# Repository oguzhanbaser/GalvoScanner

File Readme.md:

# Tubitak 1002 Projesi kapsamında geliştirilen Galbo Taraycılı Haberleşme Sistemi

## Genel Amaç
Galvo tabanlı optik yönlendirme, kamera kalibrasyonu, lazer/LED sürücü kartları ve simülasyon (Gazebo) bileşenlerini içeren çok bileşenli Ar-Ge çalışma alanı.

## Dizın Özeti
```
Softwares/
  calib_images/        (İlk kamera kalibrasyon ham görüntüleri)
  new_calib/           (Yeni kalibrasyon çekimleri)
  images/              (Deney / mesafe / çıktı görüntü setleri)
  esp_software/
    main_drv8825.cpp.bak.cpp   (DRV8825 step/dir sürücüsü için yedek ana kod)
    esp32-stepper/             (PlatformIO ESP32 step motor kontrol projesi)
    python-test/
      test1.py                 (Seri / kontrol test scripti)
      myenv*/                  (Yerel sanal ortam klasörleri - repoda tutulması gerekmez)
  opencv-ws/
    camera_calib.py            (Genel kalibrasyon scripti)
    camera_calib_real.py       (Gerçek donanım verisi ile kalibrasyon)
    camera_params.py           (Örnek/çıktı parametre dosyası)
    camera_params_rpi.py       (Raspberry Pi için parametre varyasyonu)
    find_focal_len.py          (Odak uzunluğu yaklaşık hesabı)
    my_utils.py                (Ortak yardımcı fonksiyonlar)
    test*.py / test*_iter.py   (Deneme / iteratif test scriptleri)
    images/, files/, __pycache__/ (Veri ve derleme çıktıları)
  rpi_calib/
    calib_images/              (Raspberry Pi kamera kalibrasyon görüntüleri)

Gazebo-Sim/
  my_test_pkg/
    CMakeLists.txt             (ROS paketi derleme tanımı)
    package.xml                (ROS paket meta verisi)
    launch/camera_gazebo.launch (Kamera modelini Gazebo’da başlatma)
    urdf/camera_model.xacro    (Parametrik kamera URDF/Xacro modeli)
    src/                       (Şu an boş / ileride eklenecek)

Devreler/
  beacon_led/
    led_tester*/               (LED test kartı revizyonları - KiCad .kicad_pcb/.kicad_sch)
    led_tester_v2/led_cnc/     (CNC üretim G-code çıktıları)
    led_tester_v2/production/  (BOM, konum, gerber paketleri)
  esp_stepper/
    esp_stepper.*              (ESP tabanlı stepper sürücü kart şematik & PCB)
    kicad_esp/                 (Espressif kütüphane paketi - footprint/simge)
    libs/pcb, libs/sch         (Özel footprint/schematic kütüphaneleri)
    outputs/                   (PDF çizimler)
    production/                (Üretim dosyaları, yedekler)
  laser_com/
    board/                     (Ön/alternatif ethernet tabanlı taslak kart)
    laser_com_v1/              (Lazer iletişim kartı modüler şemalar: laser_driver, regulator, step_up, fotodiyot)
    production/, output/, libs/ (Üretim & kütüphane)

```

## Önemli Bileşenler
- Kamera Kalibrasyonu: Softwares/opencv-ws/* (Chessboard / iç parametre türetme)
- ESP32 Step Motor Kontrolü: Softwares/esp_software/esp32-stepper (Galvo veya mekanik tarayıcı prototip sürüşü)
- Donanım Kartları: Devreler/* (LED beacon, stepper sürücü, lazer iletişim)
- Simülasyon: Gazebo-Sim/my_test_pkg (Kamera modelleme & ileride galvo sim eklenebilir)
- Kalibrasyon Görselleri: calib_images, new_calib, rpi_calib/calib_images (Distorsiyon/fütür LUT üretim girdileri)

## Kurulum (ESP32 Firmware - PlatformIO)
```
cd Softwares/esp_software/esp32-stepper
pio run
pio run -t upload
pio device monitor
```

## Kamera Kalibrasyon Akışı (Örnek)
1. Satranç tahtası görüntülerini calib_images/ veya new_calib/ altına koy.  
2. opencv-ws dizinine geç:
```
cd Softwares/opencv-ws
python camera_calib.py
```
3. Üretilen parametreleri (örn. camera_params.py) uygulama tarafında içe aktar.  
4. Raspberry Pi için ayrı parametre gerekirse camera_params_rpi.py referans alınır.

## Gazebo Simülasyonu
```
cd Gazebo-Sim/my_test_pkg
# ROS ortamını kaynakla (ör: source /opt/ros/<distro>/setup.bash)
roslaunch my_test_pkg camera_gazebo.launch
```
camera_model.xacro içindeki parametrelerle sanal kamera testleri yapılır.

## Donanım Üretim Notları
- production/ klasörleri: BOM (bom.csv), yerleşim (positions.csv), gerber paketleri (.zip)
- pcb & sch kütüphane dosyalarını libs/ altına izole ederek sürüm kontrolü yapılmış.
- Büyük revizyonlarda outputs/ PDF çizimleri referans saklama.

## Temizlik / .gitignore Önerisi
Aşağıdakiler repoda tutulmayabilir:
- __pycache__/, *.pyc
- Softwares/esp_software/esp32-stepper/.pio/
- Softwares/esp_software/python-test/myenv*/ (sanal ortamlar)
- Büyük ham görüntüler (Git LFS ile: *.jpg)

Örnek ekleme:
```
__pycache__/
*.pyc
.pio/
myenv*/
*.bak.*
```

## Olası Geliştirmeler
- Otomatik kalibrasyon raporu (Markdown çıktısı)
- Galvo açı ↔ piksel koordinat eşleştirme modülü
- ROS düğümü: gerçek donanım + simülasyon arayüzü
- Lazer iletişim protokol dokümantasyonu (ayrı docs/ önerilir)

## Lisans
(Lisans dosyası eklenmeli: MIT / Apache-2.0 / GPL seçilmemiş.)

## Katkı
Fork -> feature branch -> PR.  
İsimlendirme: feat-*, fix-*, doc-*.

## Uyarı
main_drv8825.cpp.bak.cpp ve büyük görüntü setleri sürüm geçmişini şişirebilir; gerekirse arşivleyin veya LFS.

## Hızlı Başlangıç
```
git clone <repo-url>
cd GalvoScanner
# ESP32
cd Softwares/esp_software/esp32-stepper && pio run
# Kalibrasyon
cd ../../opencv-ws && python camera_calib.py
```

## İletişim
Sorumlu / Ekip: (ekleyin)  
E-posta: (ekleyin)

---
Bu README mevcut görünen dizin yapısına göre derlenmiştir; yeni klasörler eklendikçe güncellenmelidir.

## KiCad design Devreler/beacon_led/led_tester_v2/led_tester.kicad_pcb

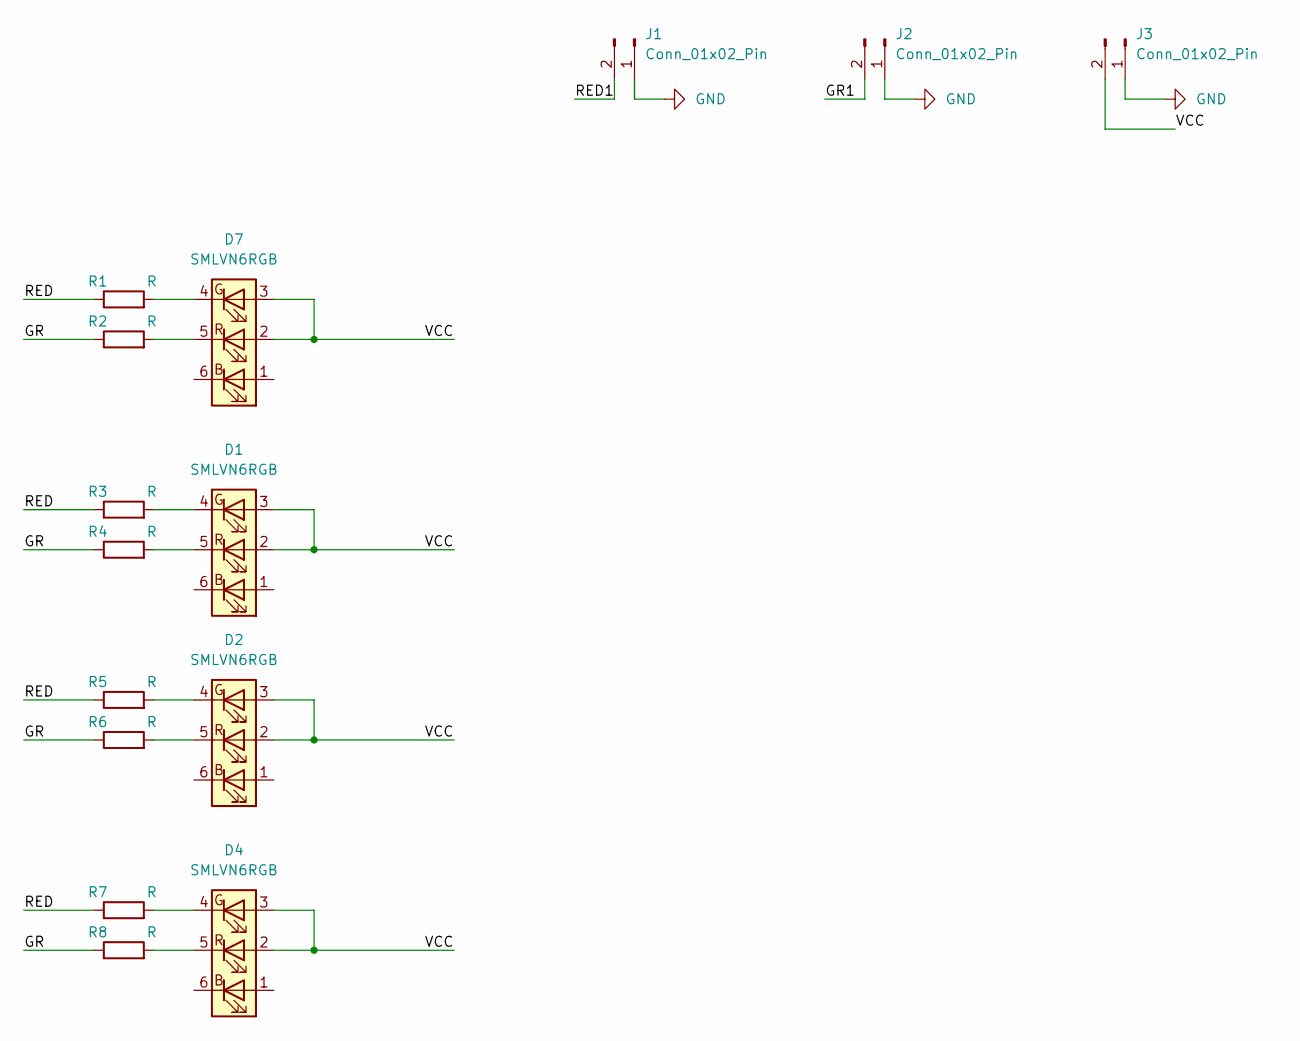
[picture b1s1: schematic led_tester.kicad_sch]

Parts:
D1, D2, D4, D7: SMLVN6RGB; LED_RGB_5050-6-HandSolder
J1, J2, J3: Conn_01x02_Pin; PinHeader_1x02_P2.54mm_Vertical
R1, R2, R3, R4, R5, R6, R7, R8: R; R_0805_2012Metric_Pad1.20x1.40mm_HandSolder

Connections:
/GR: R2.1, R4.1, R6.1, R8.1
/GR1: J2.2
/RED: R1.1, R3.1, R5.1, R7.1
/RED1: J1.2
/VCC: D1.2 (RA), D1.3 (GA), D2.2 (RA), D2.3 (GA), D4.2 (RA), D4.3 (GA), D7.2 (RA), D7.3 (GA), J3.2
GND: J1.1, J2.1, J3.1
unnamed: D1.4 (GK), R3.2
unnamed: D1.5 (RK), R4.2
unnamed: D2.4 (GK), R5.2
unnamed: D2.5 (RK), R6.2
unnamed: D4.4 (GK), R7.2
unnamed: D4.5 (RK), R8.2
unnamed: D7.4 (GK), R1.2
unnamed: D7.5 (RK), R2.2

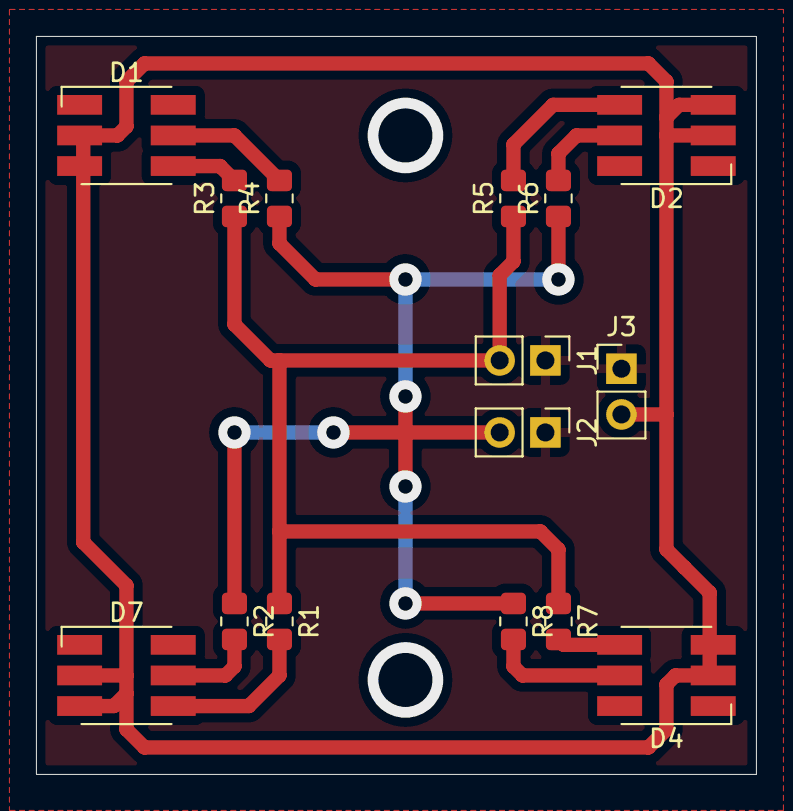
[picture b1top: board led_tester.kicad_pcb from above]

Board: 2 copper layers, 40.0 x 41.0 mm, 15 parts (0 on the bottom side), 12 nets.

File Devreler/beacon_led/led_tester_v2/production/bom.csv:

Designator,Footprint,Quantity,Value,LCSC Part #
"D1, D2, D4, D7",LED_RGB_5050-6-HandSolder,4,SMLVN6RGB,
"J1, J2, J3",PinHeader_1x02_P2.54mm_Vertical,3,Conn_01x02_Pin,
"R1, R2, R3, R4, R5, R6, R7, R8",0805,8,R,

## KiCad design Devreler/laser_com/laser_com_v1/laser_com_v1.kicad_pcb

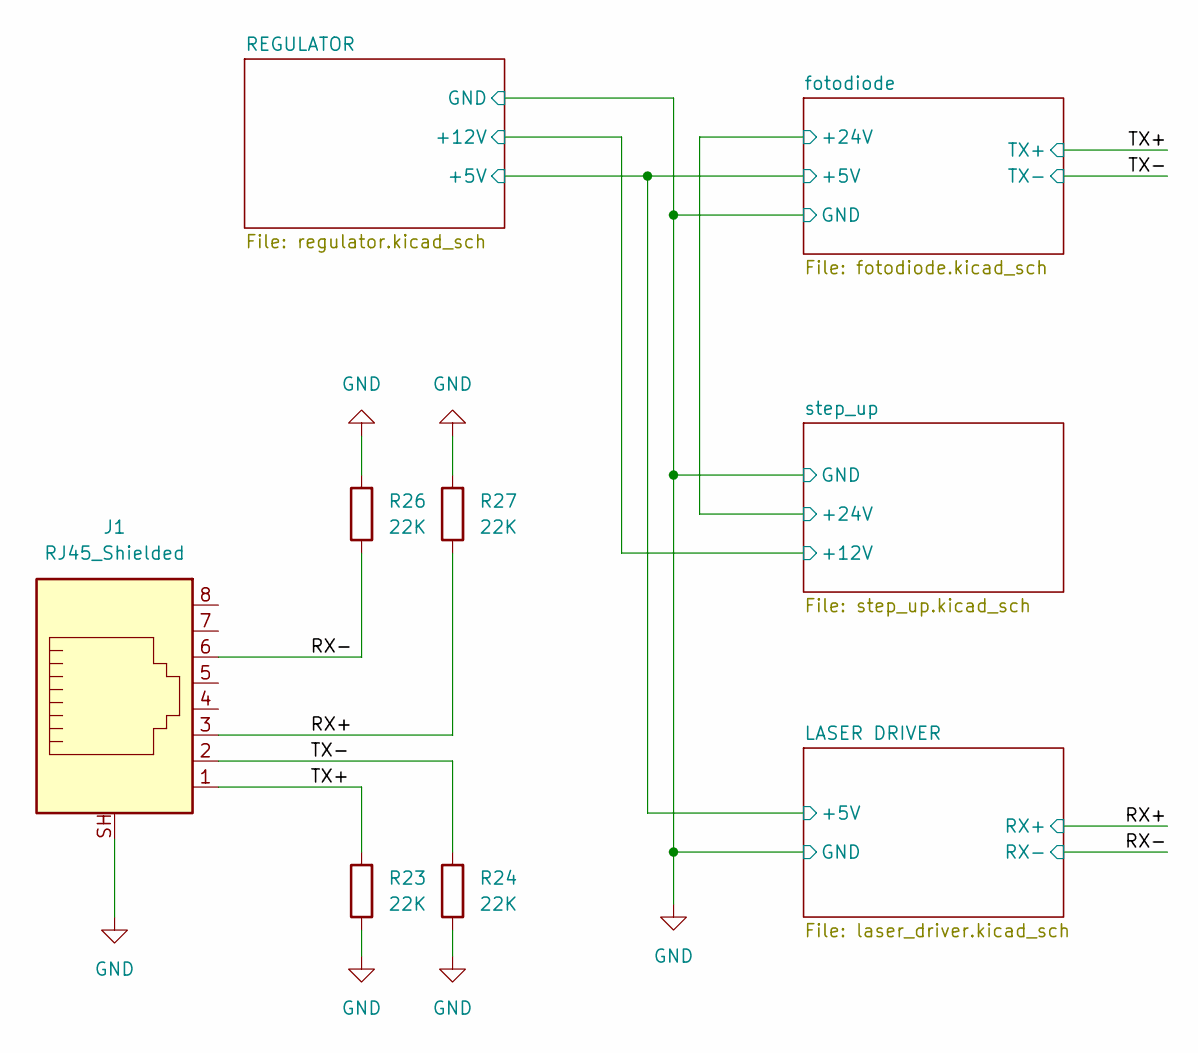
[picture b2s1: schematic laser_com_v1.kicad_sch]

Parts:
J1: RJ45_Shielded; RJ45_Amphenol_RJHSE5380
R23, R24, R26, R27: 22K; R_0805_2012Metric_Pad1.20x1.40mm_HandSolder

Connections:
/RX+: J1.3, R27.1; also elsewhere on the board
/RX-: J1.6, R26.1; also elsewhere on the board
/TX+: J1.1, R23.2; also elsewhere on the board
/TX-: J1.2, R24.2; also elsewhere on the board
GND: J1.SH, R23.1, R24.1, R26.2, R27.2; also elsewhere on the board

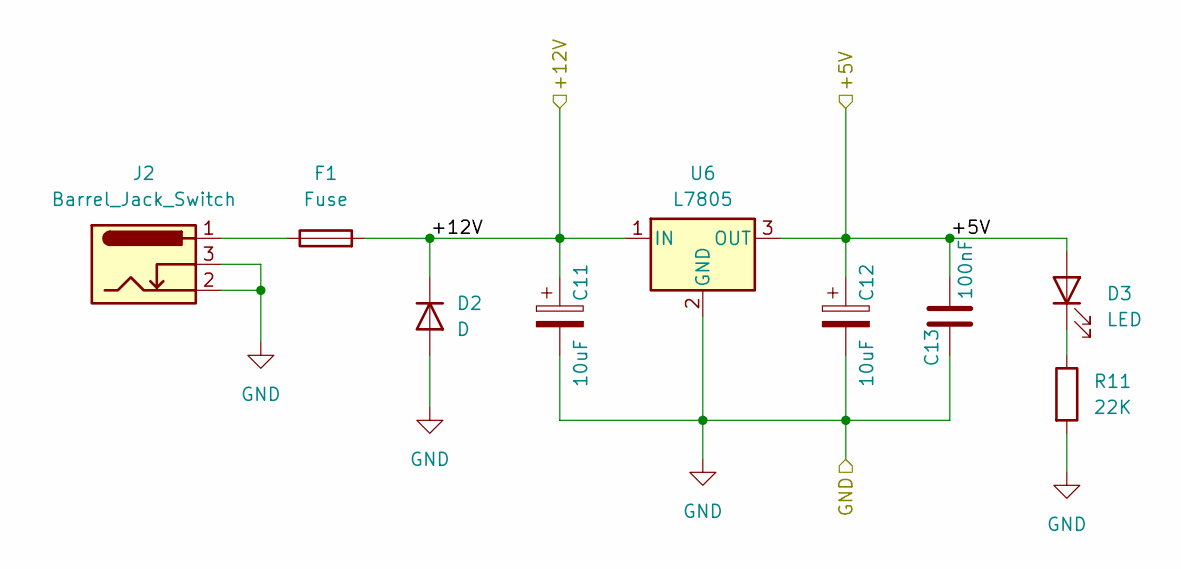
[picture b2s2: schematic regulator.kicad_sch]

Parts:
C11, C12: 10uF; CP_EIA-3216-18_Kemet-A
C13: 100nF; C_0805_2012Metric_Pad1.18x1.45mm_HandSolder
D2: D; D_SMA
D3: LED; LED_0805_2012Metric_Pad1.15x1.40mm_HandSolder
F1: Fuse; Fuse_1206_3216Metric
J2: Barrel_Jack_Switch; BarrelJack_GCT_DCJ200-10-A_Horizontal
R11: 22K; R_0805_2012Metric_Pad1.20x1.40mm_HandSolder
U6: L7805; TO-252-2

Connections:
/LASER DRIVER/+5V: C12.1, C13.1, D3.2 (A), U6.3 (OUT); also elsewhere on the board
/REGULATOR/+12V: C11.1, D2.1 (K), F1.2, U6.1 (IN); also elsewhere on the board
GND: C11.2, C12.2, C13.2, D2.2 (A), J2.2, J2.3, R11.2, U6.2 (GND); also elsewhere on the board
unnamed: D3.1 (K), R11.1
unnamed: F1.1, J2.1

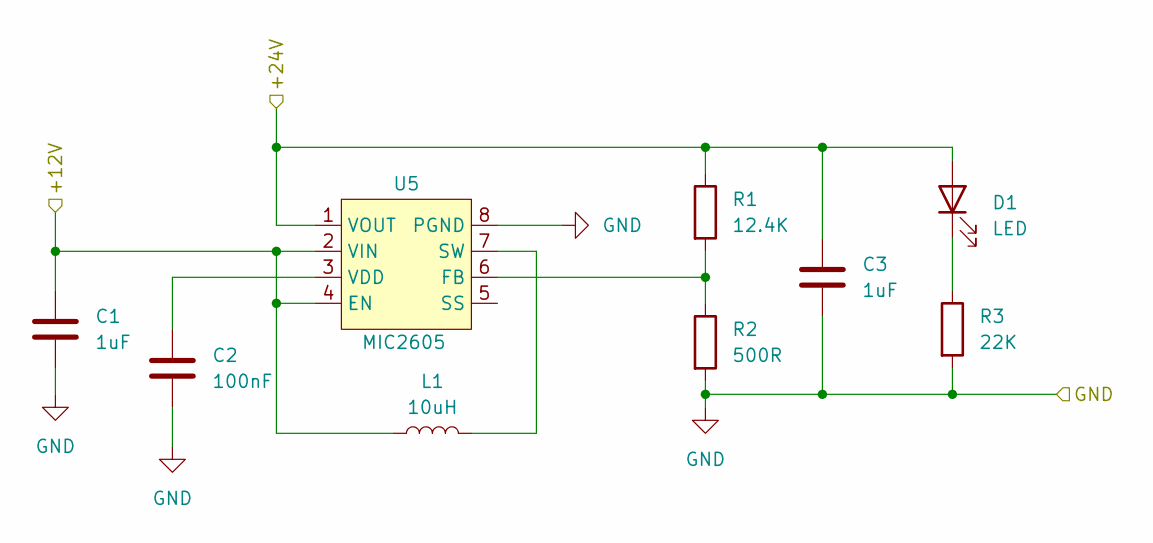
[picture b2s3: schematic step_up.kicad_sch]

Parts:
C1, C3: 1uF; C_0805_2012Metric_Pad1.18x1.45mm_HandSolder
C2: 100nF; C_0805_2012Metric_Pad1.18x1.45mm_HandSolder
D1: LED; LED_0805_2012Metric_Pad1.15x1.40mm_HandSolder
L1: 10uH; L_1206_3216Metric_Pad1.42x1.75mm_HandSolder
R1: 12.4K; R_0805_2012Metric_Pad1.20x1.40mm_HandSolder
R2: 500R; R_0805_2012Metric_Pad1.20x1.40mm_HandSolder
R3: 22K; R_0805_2012Metric_Pad1.20x1.40mm_HandSolder
U5: MIC2605; TDFN-8-1EP_2x2mm_P0.5mm_EP0.8x1.2mm

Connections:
/REGULATOR/+12V: C1.1, L1.1, U5.2 (VIN), U5.4 (EN); also elsewhere on the board
/fotodiode/+24V: C3.1, D1.2 (A), R1.1, U5.1 (VOUT); also elsewhere on the board
GND: C1.2, C2.2, C3.2, R2.2, R3.2, U5.8 (PGND); also elsewhere on the board
unnamed: D1.1 (K), R3.1
unnamed: R1.2, R2.1, U5.6 (FB)
unnamed: L1.2, U5.7 (SW)
unnamed: C2.1, U5.3 (VDD)

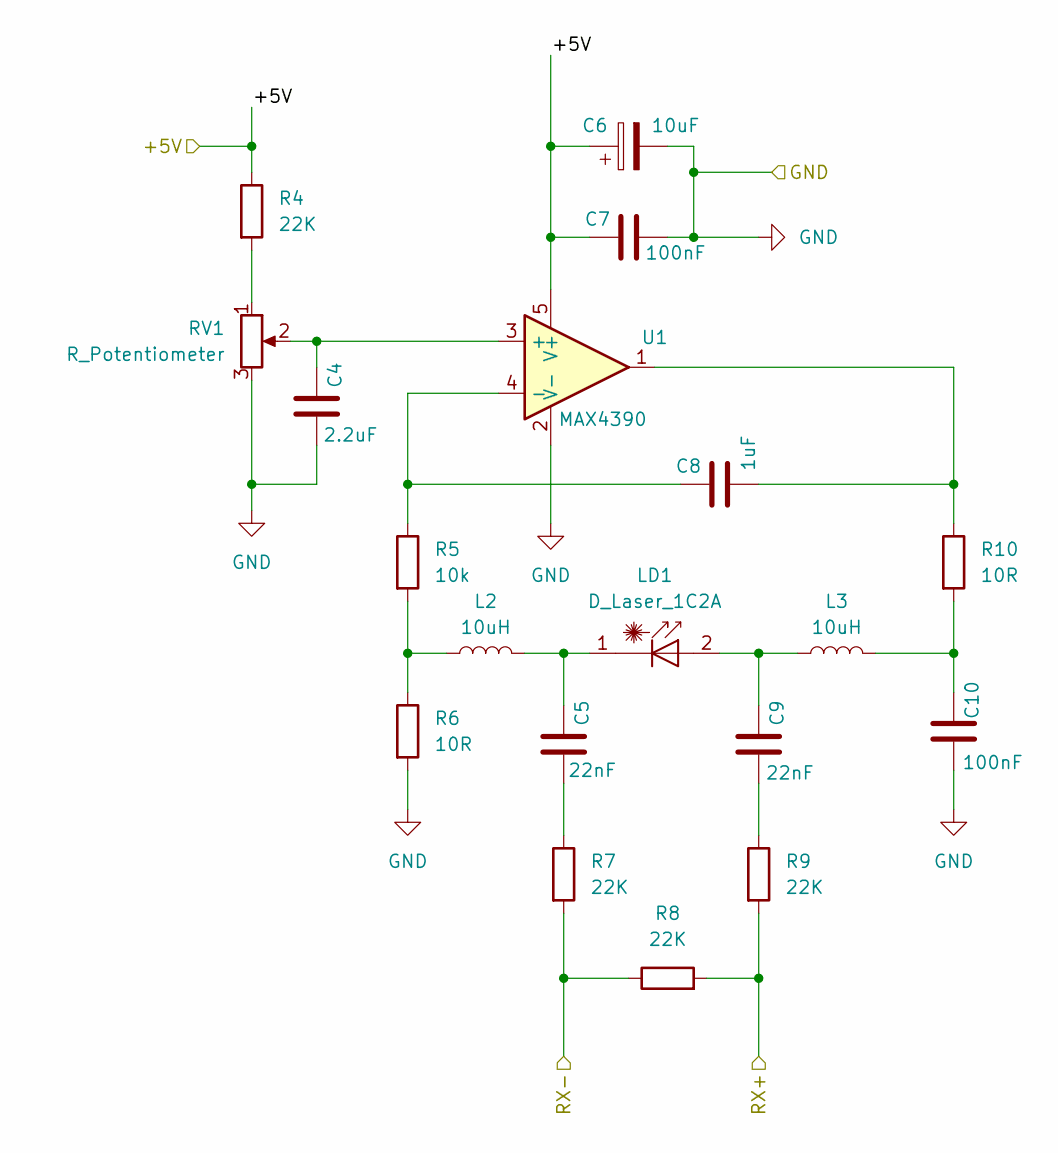
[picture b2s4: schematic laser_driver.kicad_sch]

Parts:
C4: 2.2uF; C_0805_2012Metric_Pad1.18x1.45mm_HandSolder
C5, C9: 22nF; C_0805_2012Metric_Pad1.18x1.45mm_HandSolder
C6: 10uF; CP_EIA-3216-18_Kemet-A
C7, C10: 100nF; C_0805_2012Metric_Pad1.18x1.45mm_HandSolder
C8: 1uF; C_0805_2012Metric_Pad1.18x1.45mm_HandSolder
L2, L3: 10uH; L_1206_3216Metric_Pad1.42x1.75mm_HandSolder
LD1: D_Laser_1C2A; PinHeader_1x02_P2.54mm_Vertical
R4, R7, R8, R9: 22K; R_0805_2012Metric_Pad1.20x1.40mm_HandSolder
R5: 10k; R_0805_2012Metric_Pad1.20x1.40mm_HandSolder
R6, R10: 10R; R_0805_2012Metric_Pad1.20x1.40mm_HandSolder
RV1: R_Potentiometer; Potentiometer_Bourns_TC33X_Vertical
U1: MAX4390; SOT-23-5_HandSoldering

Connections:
/LASER DRIVER/+5V: C6.1, C7.2, R4.1, U1.5 (V+); also elsewhere on the board
/RX+: R8.2, R9.2; also elsewhere on the board
/RX-: R7.2, R8.1; also elsewhere on the board
GND: C4.1, C6.2, C7.1, C10.1, R6.2, RV1.3, U1.2 (V-); also elsewhere on the board
unnamed: C5.1, R7.1
unnamed: C8.1, R10.1, U1.1
unnamed: C9.1, R9.1
unnamed: C10.2, L3.2, R10.2
unnamed: L2.1, R5.2, R6.1
unnamed: C9.2, L3.1, LD1.2 (A)
unnamed: C5.2, L2.2, LD1.1 (K)
unnamed: R4.2, RV1.1
unnamed: C4.2, RV1.2, U1.3 (+)
unnamed: C8.2, R5.1, U1.4 (-)

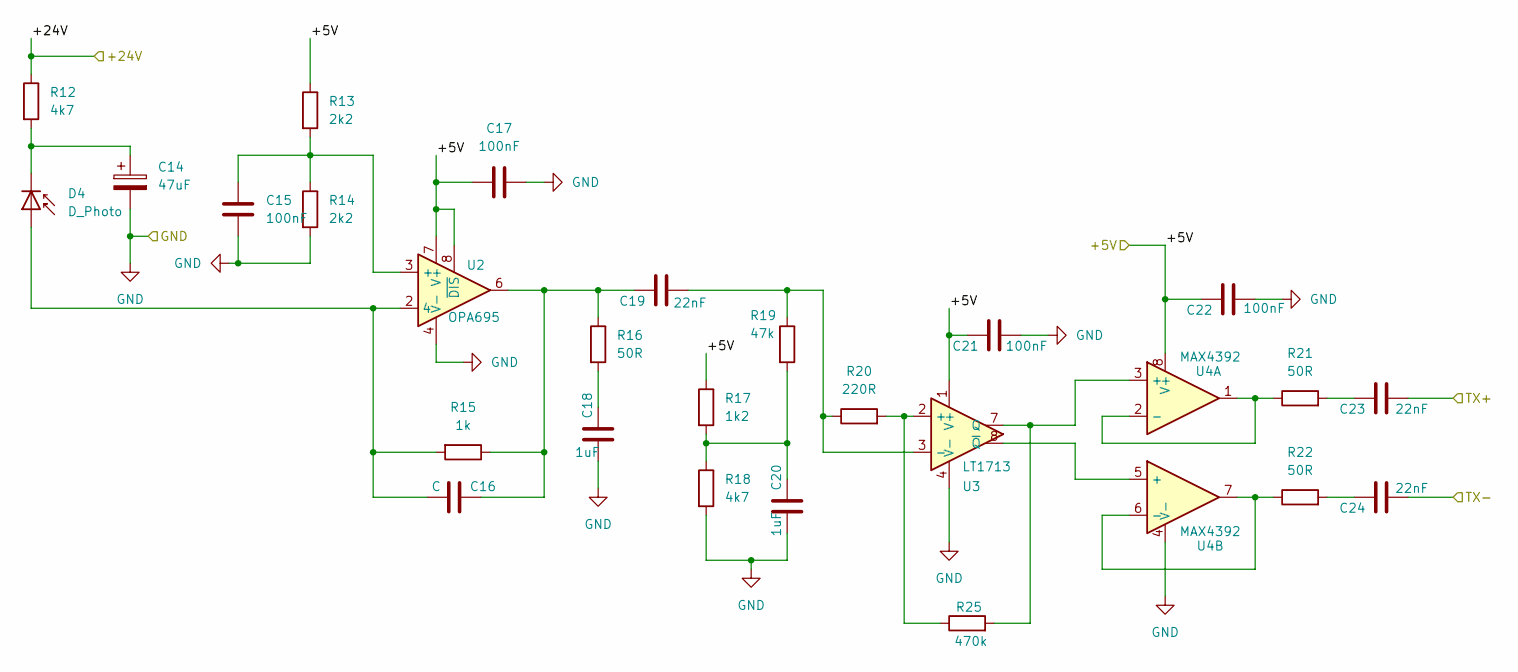
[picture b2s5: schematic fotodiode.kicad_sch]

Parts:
C14: 47uF; CP_EIA-3216-18_Kemet-A
C15, C17, C21, C22: 100nF; C_0805_2012Metric_Pad1.18x1.45mm_HandSolder
C16: C; C_0805_2012Metric_Pad1.18x1.45mm_HandSolder
C18, C20: 1uF; C_0805_2012Metric_Pad1.18x1.45mm_HandSolder
C19, C23, C24: 22nF; C_0805_2012Metric_Pad1.18x1.45mm_HandSolder
D4: D_Photo; PinHeader_2x01_P2.54mm_Vertical
R12, R18: 4k7; R_0805_2012Metric_Pad1.20x1.40mm_HandSolder
R13, R14: 2k2; R_0805_2012Metric_Pad1.20x1.40mm_HandSolder
R15: 1k; R_0805_2012Metric_Pad1.20x1.40mm_HandSolder
R16, R21, R22: 50R; R_0805_2012Metric_Pad1.20x1.40mm_HandSolder
R17: 1k2; R_0805_2012Metric_Pad1.20x1.40mm_HandSolder
R19: 47k; R_0805_2012Metric_Pad1.20x1.40mm_HandSolder
R20: 220R; R_0805_2012Metric_Pad1.20x1.40mm_HandSolder
R25: 470k; R_0805_2012Metric_Pad1.20x1.40mm_HandSolder
U2: OPA695; SOIC-8_3.9x4.9mm_P1.27mm
U3: LT1713; MSOP-8_3x3mm_P0.65mm
U4: MAX4392; SOP65P490X110-8N

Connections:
/LASER DRIVER/+5V: C17.2, C21.2, C22.2, R13.1, R17.1, U2.7 (V+), U2.8 (~DIS), U3.1 (V+), U4.8 (V+); also elsewhere on the board
/TX+: C23.1; also elsewhere on the board
/TX-: C24.1; also elsewhere on the board
/fotodiode/+24V: R12.1; also elsewhere on the board
GND: C14.2, C15.2, C17.1, C18.1, C20.1, C21.1, C22.1, R14.2, R18.2, U2.4 (V-), U3.4 (V-), U4.4 (V-); also elsewhere on the board
unnamed: C16.2, C19.2, R15.1, R16.1, U2.6
unnamed: C18.2, R16.2
unnamed: C20.2, R17.2, R18.1, R19.2
unnamed: C23.2, R21.2
unnamed: C24.2, R22.2
unnamed: C16.1, D4.2 (A), R15.2, U2.2 (4)
unnamed: C14.1, D4.1 (K), R12.2
unnamed: C15.1, R13.2, R14.1, U2.3 (+)
unnamed: R20.2, R25.1, U3.2 (+)
unnamed: C19.1, R19.1, R20.1, U3.3 (-)
unnamed: R25.2, U3.7 (Q), U4.3 (+)
unnamed: U3.8 (~Q), U4.5 (+)
unnamed: R21.1, U4.1, U4.2 (-)
unnamed: R22.1, U4.6 (-), U4.7

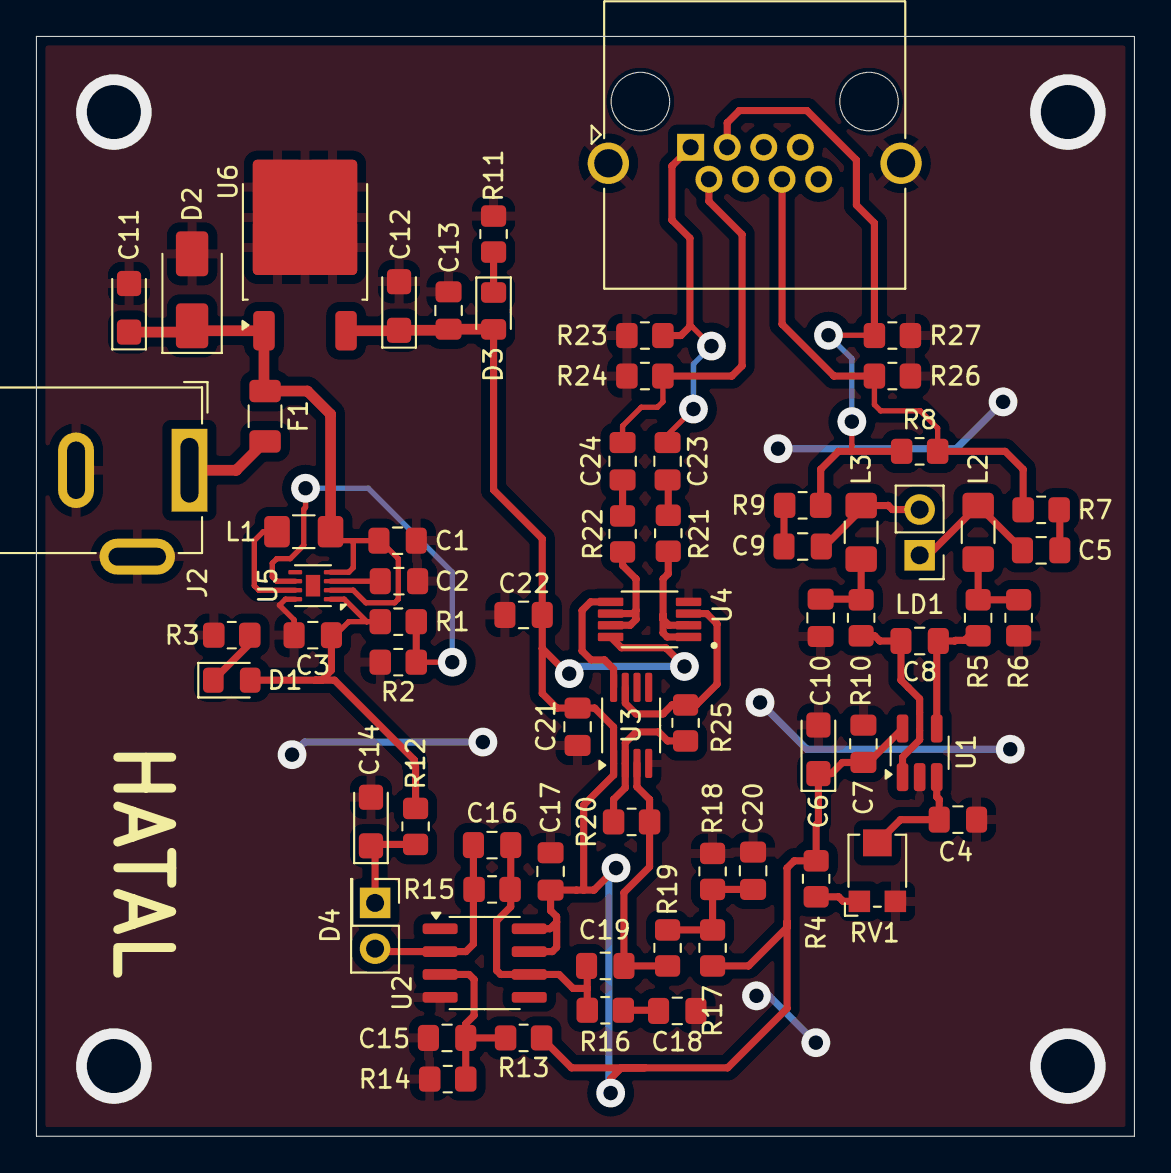
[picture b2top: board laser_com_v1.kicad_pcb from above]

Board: 2 copper layers, 61.0 x 61.1 mm, 69 parts (0 on the bottom side), 38 nets.

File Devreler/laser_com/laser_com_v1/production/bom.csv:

Designator,Footprint,Quantity,Value,LCSC Part #
"C1, C18, C20, C3, C8",0805,5,1uF,
"C10, C13, C15, C17, C2, C21, C22, C7",0805,8,100nF,
"C11, C12, C6",CP_EIA-3216-18_Kemet-A,3,10uF,
C14,CP_EIA-3216-18_Kemet-A,1,47uF,
C16,0805,1,C,
"C19, C23, C24, C5, C9",0805,5,22nF,
C4,0805,1,2.2uF,
"D1, D3",0805,2,LED,
D2,D_SMA,1,D,
D4,PinHeader_2x01_P2.54mm_Vertical,1,D_Photo,
F1,1206,1,Fuse,
J1,RJ45_Amphenol_RJHSE5380,1,RJ45_Shielded,
J2,BarrelJack_GCT_DCJ200-10-A_Horizontal,1,Barrel_Jack_Switch,
"L1, L2, L3",1206,3,10uH,
LD1,PinHeader_1x02_P2.54mm_Vertical,1,D_Laser_1C2A,
R1,0805,1,12.4K,
"R10, R6",0805,2,10R,
"R11, R23, R24, R26, R27, R3, R4, R7, R8, R9",0805,10,22K,
"R12, R18",0805,2,4k7,
"R13, R14",0805,2,2k2,
R15,0805,1,1k,
"R16, R21, R22",0805,3,50R,
R17,0805,1,1k2,
R19,0805,1,47k,
R2,0805,1,500R,
R20,0805,1,220R,
R25,0805,1,470k,
R5,0805,1,10k,
RV1,Potentiometer_Bourns_TC33X_Vertical,1,R_Potentiometer,
U1,SOT-23-5_HandSoldering,1,MAX4390,
U2,SOIC-8_3.9x4.9mm_P1.27mm,1,OPA695,
U3,MSOP-8_3x3mm_P0.65mm,1,LT1713,
U4,SOP65P490X110-8N,1,MAX4392,
U5,TDFN-8-1EP_2x2mm_P0.5mm_EP0.8x1.2mm,1,MIC2605,
U6,TO-252-2,1,L7805,

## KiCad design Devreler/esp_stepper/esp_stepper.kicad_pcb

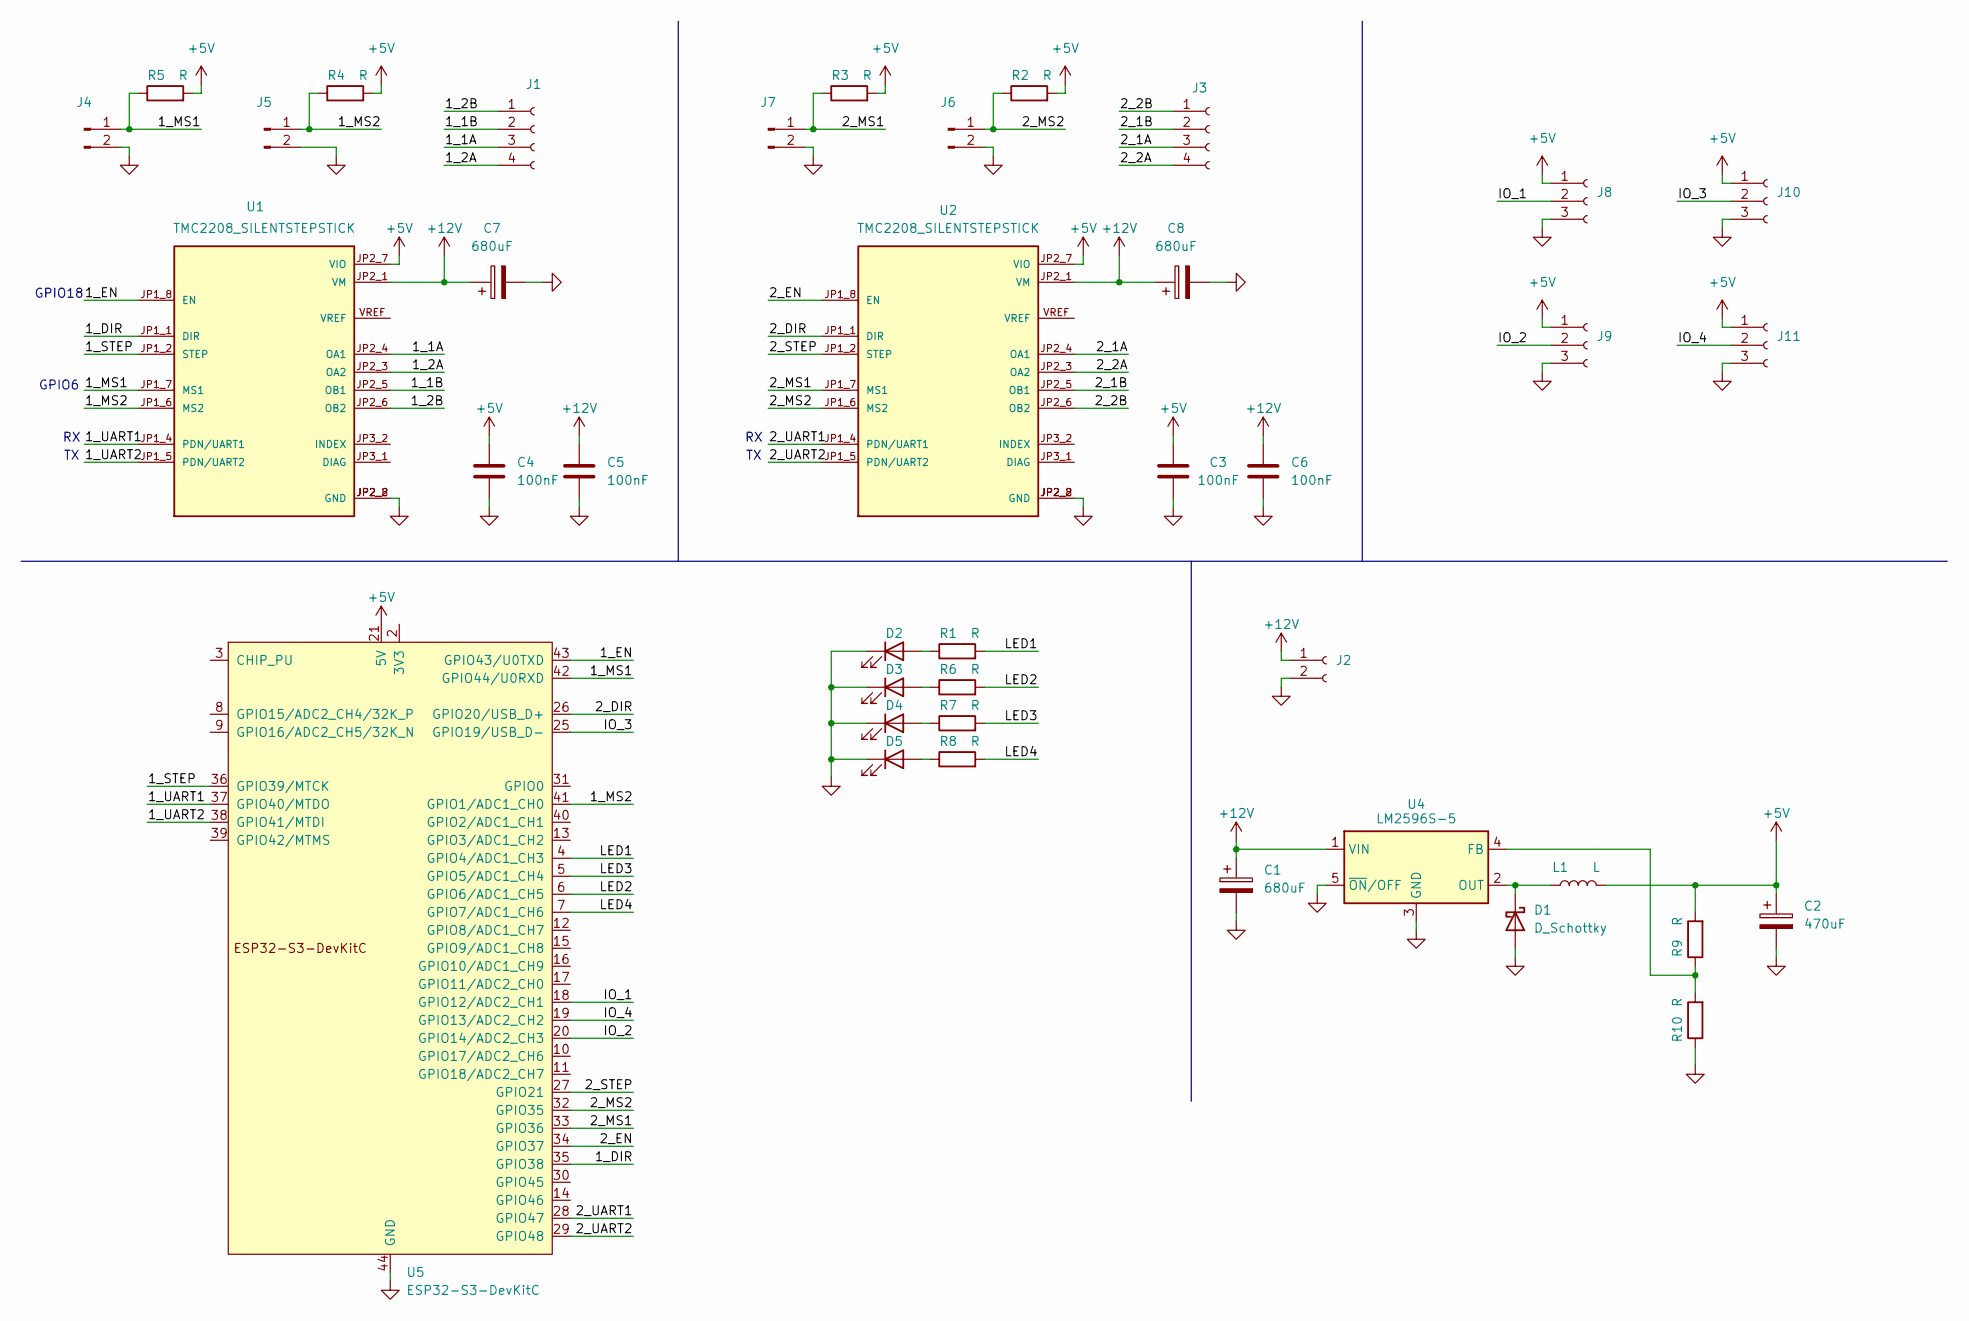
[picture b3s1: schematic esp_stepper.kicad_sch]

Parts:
C1, C7, C8: 680uF; CP_Radial_D8.0mm_P5.00mm
C2: 470uF; CP_Radial_D8.0mm_P5.00mm
C3, C4, C5, C6: 100nF; C_0805_2012Metric_Pad1.18x1.45mm_HandSolder
D1: D_Schottky; D_SMB_Handsoldering
D2, D3, D4, D5: LED; LED_D5.0mm
J1, J3: Conn_01x04_Socket; TerminalBlock_Phoenix_MKDS-1,5-4_1x04_P5.00mm_Horizontal
J2: Conn_01x02_Socket; TerminalBlock_Phoenix_MKDS-1,5-2-5.08_1x02_P5.08mm_Horizont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
J4, J5, J6, J7: Conn_01x02_Pin; PinHeader_1x02_P2.54mm_Vertical
J8, J9, J10, J11: Conn_01x03_Socket; PinHeader_1x03_P2.54mm_Vertical
L1: L; L_7.3x7.3_H4.5
R1, R2, R3, R4, R5, R6, R7, R8, R9, R10: R; R_0805_2012Metric_Pad1.20x1.40mm_HandSolder
U1, U2: TMC2208_SILENTSTEPSTICK; MODULE_TMC2208_SILENTSTEPSTICK
U4: LM2596S-5; TO-263-5_TabPin3
U5: ESP32-S3-DevKitC

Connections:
+5V: C2.1, C3.2, C4.2, J8.1, J9.1, J10.1, J11.1, L1.2, R2.2, R3.2, R4.2, R5.2, R9.2, U1.JP2_7 (VIO), U2.JP2_7 (VIO), U5.21 (5V)
+12V: C1.1, C5.2, C6.2, C7.1, C8.1, J2.1, U1.JP2_1 (VM), U2.JP2_1 (VM), U4.1 (VIN)
/1_1A: J1.3, U1.JP2_4 (OA1)
/1_1B: J1.2, U1.JP2_5 (OB1)
/1_2A: J1.4, U1.JP2_3 (OA2)
/1_2B: J1.1, U1.JP2_6 (OB2)
/1_DIR: U1.JP1_1 (DIR), U5.35 (GPIO38)
/1_EN: U1.JP1_8 (EN), U5.43 (GPIO43/U0TXD)
/1_MS1: J4.1, R5.1, U1.JP1_7 (MS1), U5.42 (GPIO44/U0RXD)
/1_MS2: J5.1, R4.1, U1.JP1_6 (MS2), U5.41 (GPIO1/ADC1_CH0)
/1_STEP: U1.JP1_2 (STEP), U5.36 (GPIO39/MTCK)
/1_UART1: U1.JP1_4 (PDN/UART1), U5.37 (GPIO40/MTDO)
/1_UART2: U1.JP1_5 (PDN/UART2), U5.38 (GPIO41/MTDI)
/2_1A: J3.3, U2.JP2_4 (OA1)
/2_1B: J3.2, U2.JP2_5 (OB1)
/2_2A: J3.4, U2.JP2_3 (OA2)
/2_2B: J3.1, U2.JP2_6 (OB2)
/2_DIR: U2.JP1_1 (DIR), U5.26 (GPIO20/USB_D+)
/2_EN: U2.JP1_8 (EN), U5.34 (GPIO37)
/2_MS1: J7.1, R3.1, U2.JP1_7 (MS1), U5.33 (GPIO36)
/2_MS2: J6.1, R2.1, U2.JP1_6 (MS2), U5.32 (GPIO35)
/2_STEP: U2.JP1_2 (STEP), U5.27 (GPIO21)
/2_UART1: U2.JP1_4 (PDN/UART1), U5.28 (GPIO47)
/2_UART2: U2.JP1_5 (PDN/UART2), U5.29 (GPIO48)
/IO_1: J8.2, U5.18 (GPIO12/ADC2_CH1)
/IO_2: J9.2, U5.20 (GPIO14/ADC2_CH3)
/IO_3: J10.2, U5.25 (GPIO19/USB_D-)
/IO_4: J11.2, U5.19 (GPIO13/ADC2_CH2)
/LED1: R1.2, U5.4 (GPIO4/ADC1_CH3)
/LED2: R6.2, U5.6 (GPIO6/ADC1_CH5)
/LED3: R7.2, U5.5 (GPIO5/ADC1_CH4)
/LED4: R8.2, U5.7 (GPIO7/ADC1_CH6)
GND: C1.2, C2.2, C3.1, C4.1, C5.1, C6.1, C7.2, C8.2, D1.2 (A), D2.1 (K), D3.1 (K), D4.1 (K), D5.1 (K), J2.2, J4.2, J5.2, J6.2, J7.2, J8.3, J9.3, J10.3, J11.3, R10.1, U1.JP2_2 (GND), U1.JP2_8 (GND), U2.JP2_2 (GND), U2.JP2_8 (GND), U4.3 (GND), U4.5 (~ON/OFF), U5.22 (GND), U5.23 (GND), U5.24 (GND), U5.44 (GND)
unnamed: D1.1 (K), L1.1, U4.2 (OUT)
unnamed: D2.2 (A), R1.1
unnamed: D3.2 (A), R6.1
unnamed: D4.2 (A), R7.1
unnamed: D5.2 (A), R8.1
unnamed: R9.1, R10.2, U4.4 (FB)
unnamed: U5.1 (3V3), U5.2 (3V3)

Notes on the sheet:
GPIO18
GPIO6

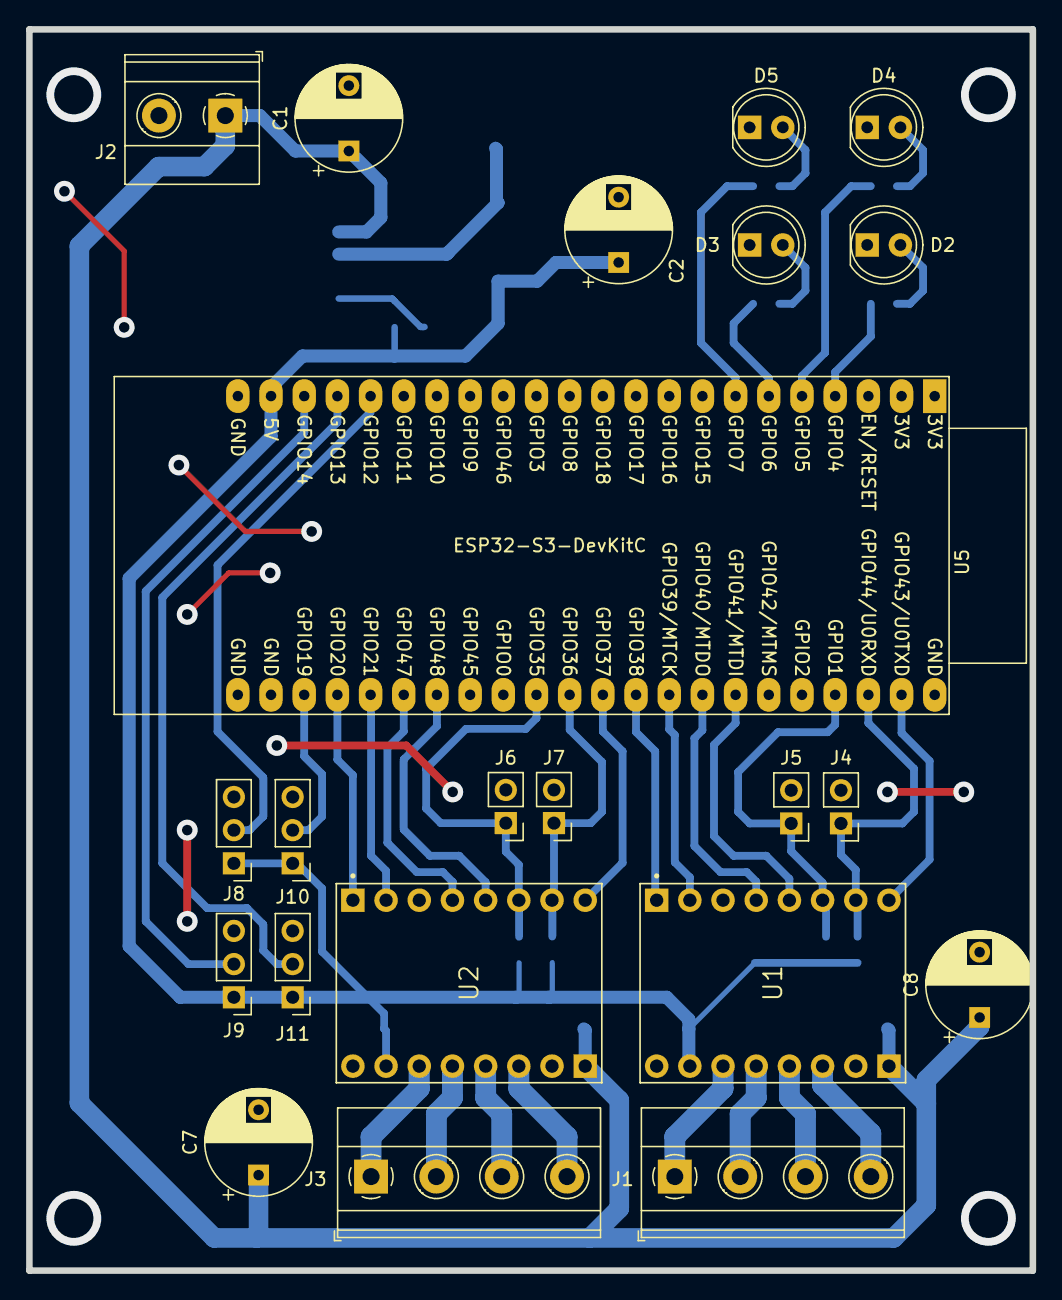
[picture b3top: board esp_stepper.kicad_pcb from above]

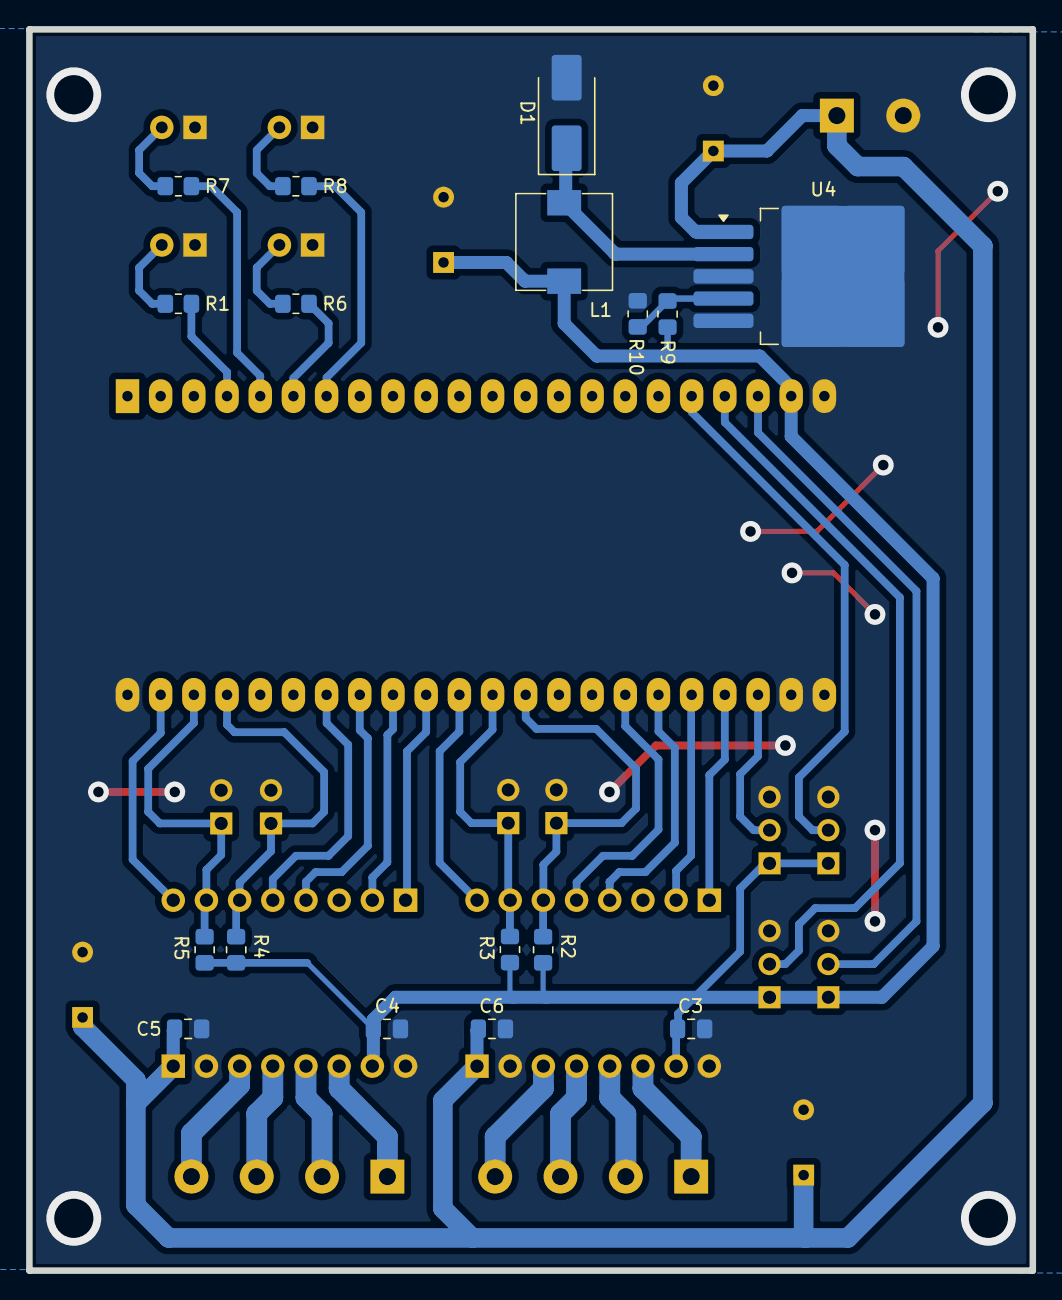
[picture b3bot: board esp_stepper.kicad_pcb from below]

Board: 2 copper layers, 76.8 x 95.0 mm, 39 parts (17 on the bottom side), 40 nets.

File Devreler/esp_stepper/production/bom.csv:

Designator,Footprint,Quantity,Value,LCSC Part #
"C1, C7, C8",CP_Radial_D8.0mm_P5.00mm,3,680uF,
C2,CP_Radial_D8.0mm_P5.00mm,1,470uF,
"C3, C4, C5, C6",0805,4,100nF,
D1,D_SMB_Handsoldering,1,D_Schottky,
"D2, D3, D4, D5",LED_D5.0mm,4,LED,
"J1, J3","TerminalBlock_Phoenix_MKDS-1,5-4_1x04_P5.00mm_Horizontal",2,Conn_01x04_Socket,
"J10, J11, J8, J9",PinHeader_1x03_P2.54mm_Vertical,4,Conn_01x03_Socket,
J2,"TerminalBlock_Phoenix_MKDS-1,5-2-5.08_1x02_P5.08mm_Horizontal",1,Conn_01x02_Socket,
"J4, J5, J6, J7",PinHeader_1x02_P2.54mm_Vertical,4,Conn_01x02_Pin,
L1,L_7.3x7.3_H4.5,1,L,
"R1, R10, R2, R3, R4, R5, R6, R7, R8, R9",0805,10,R,
"U1, U2",MODULE_TMC2208_SILENTSTEPSTICK,2,TMC2208_SILENTSTEPSTICK,
U4,TO-263-5_TabPin3,1,LM2596S-5,
U5,ESP32-S3-DevKitC,1,ESP32-S3-DevKitC,
